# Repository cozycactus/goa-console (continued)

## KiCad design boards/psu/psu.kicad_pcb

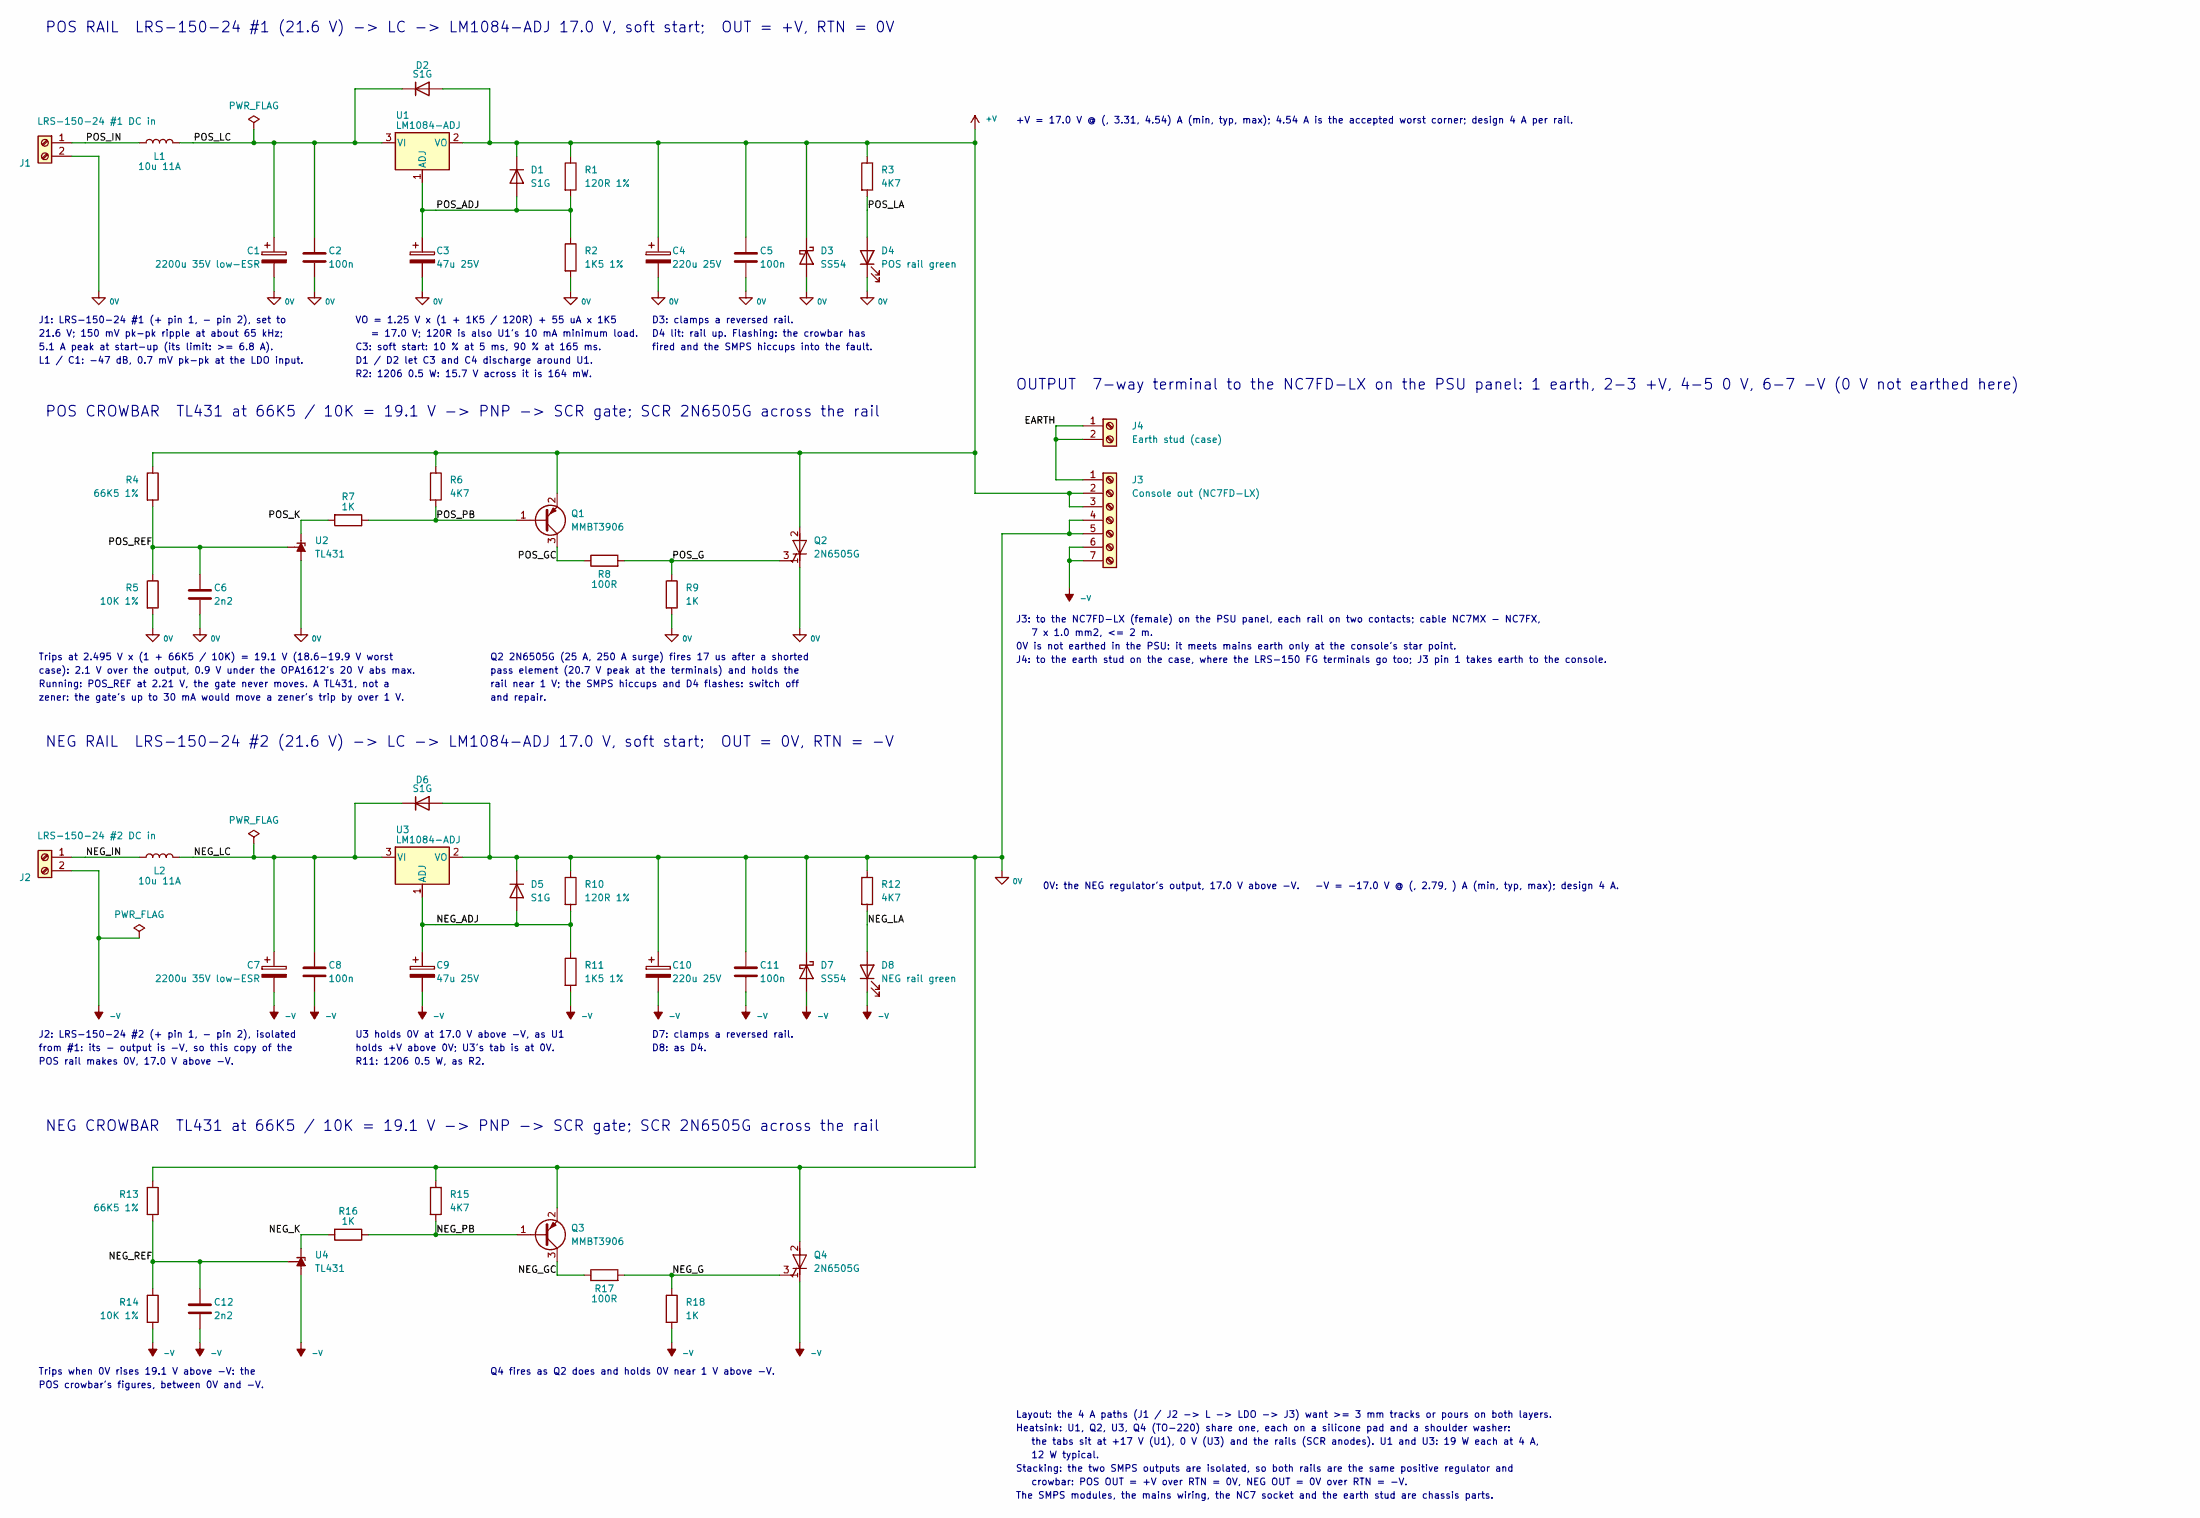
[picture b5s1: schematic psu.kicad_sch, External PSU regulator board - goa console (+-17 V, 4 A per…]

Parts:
C1, C7: 2200u 35V low-ESR; CP_Radial_D16.0mm_P7.50mm; MPN Rubycon 35ZLH2200MEFC16X25
C2, C5, C8, C11: 100n; C_0805_2012Metric; MPN Samsung CL21B104KBCNNNC (X7R 50V)
C3, C9: 47u 25V; CP_Radial_D6.3mm_P2.50mm; MPN Rubycon 63ZLH47MEFC6.3X11 (63V)
C4, C10: 220u 25V; CP_Radial_D8.0mm_P3.50mm; MPN Panasonic EEU-FR1E221
C6, C12: 2n2; C_0805_2012Metric; MPN KEMET C0805C222J5GACTU (C0G)
D1, D2, D5, D6: S1G; D_SMA; MPN Diodes S1G-13-F
D3, D7: SS54; D_SMC; MPN Diodes B540C-13-F (SS54 class, SMC 40 V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
D4: POS rail green; LED_D3.0mm; MPN Kingbright WP710A10GD
D8: NEG rail green; LED_D3.0mm; MPN Kingbright WP710A10GD
J1: LRS-150-24 #1 DC in; TerminalBlock_Phoenix_MKDS-1,5-2-5.08_1x02_P5.08mm_Horizont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; MPN Phoenix 1715721 MKDS 1,5/2-5,08
J2: LRS-150-24 #2 DC in; TerminalBlock_Phoenix_MKDS-1,5-2-5.08_1x02_P5.08mm_Horizont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; MPN Phoenix 1715721 MKDS 1,5/2-5,08
J3: Console out (NC7FD-LX); TerminalBlock_Phoenix_MKDS-1,5-7-5.08_1x07_P5.08mm_Horizont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; MPN Phoenix 1755897 MKDS 1,5/7-5,08 (to a N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
J4: Earth stud (case); TerminalBlock_Phoenix_MKDS-1,5-2-5.08_1x02_P5.08mm_Horizont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; MPN Phoenix 1715721 MKDS 1,5/2-5,08
L1, L2: 10u 11A; L_Toroid_Horizontal_D21.8mm_P19.10mm_Bourns_2100; MPN Bourns 2100LL-100-H-RC
Q1, Q3: MMBT3906; SOT-23; MPN onsemi MMBT3906LT1G
Q2, Q4: 2N6505G; TO-220-3_Vertical; MPN onsemi 2N6505G
R1, R10: 120R 1%; R_0805_2012Metric
R2, R11: 1K5 1%; R_1206_3216Metric; MPN Panasonic ERJ-P06F1501V
R3, R6, R12, R15: 4K7; R_0805_2012Metric
R4, R13: 66K5 1%; R_0805_2012Metric
R5, R14: 10K 1%; R_0805_2012Metric
R7, R9, R16, R18: 1K; R_0805_2012Metric
R8, R17: 100R; R_0805_2012Metric
U1, U3: LM1084-ADJ; TO-220-3_Vertical; MPN TI LM1084IT-ADJ/NOPB
U2, U4: TL431; SOT-23; MPN TI TL431AIDBZR

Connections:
/0V: C1.2, C2.2, C3.2, C4.2, C5.2, C6.2, C10.1, C11.1, D3.2 (A), D4.1 (K), D5.1 (K), D6.2 (A), D7.1 (K), J1.2, J3.4, J3.5, Q2.1 (K), Q3.2 (E), Q4.2 (A), R2.2, R5.2, R9.2, R10.1, R12.1, R13.1, R15.1, U2.3 (A), U3.2 (VO)
/+V: C4.1, C5.1, D1.1 (K), D2.2 (A), D3.1 (K), J3.2, J3.3, Q1.2 (E), Q2.2 (A), R1.1, R3.1, R4.1, R6.1, U1.2 (VO)
/-V: C7.2, C8.2, C9.2, C10.2, C11.2, C12.2, D7.2 (A), D8.1 (K), J2.2, J3.6, J3.7, Q4.1 (K), R11.2, R14.2, R18.2, U4.3 (A)
/EARTH: J3.1, J4.1, J4.2
/NEG_ADJ: C9.1, D5.2 (A), R10.2, R11.1, U3.1 (ADJ)
/NEG_G: Q4.3 (G), R17.2, R18.1
/NEG_GC: Q3.3 (C), R17.1
/NEG_IN: J2.1, L2.1
/NEG_K: R16.2, U4.1 (K)
/NEG_LA: D8.2 (A), R12.2
/NEG_LC: C7.1, C8.1, D6.1 (K), L2.2, U3.3 (VI)
/NEG_PB: Q3.1 (B), R15.2, R16.1
/NEG_REF: C12.1, R13.2, R14.1, U4.2 (REF)
/POS_ADJ: C3.1, D1.2 (A), R1.2, R2.1, U1.1 (ADJ)
/POS_G: Q2.3 (G), R8.2, R9.1
/POS_GC: Q1.3 (C), R8.1
/POS_IN: J1.1, L1.1
/POS_K: R7.2, U2.1 (K)
/POS_LA: D4.2 (A), R3.2
/POS_LC: C1.1, C2.1, D2.1 (K), L1.2, U1.3 (VI)
/POS_PB: Q1.1 (B), R6.2, R7.1
/POS_REF: C6.1, R4.2, R5.1, U2.2 (REF)

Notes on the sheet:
POS RAIL LRS-150-24 #1 (21.6 V) -> LC -> LM1084-ADJ 17.0 V, soft start; OUT = +V, RTN = 0V
POS CROWBAR TL431 at 66K5 / 10K = 19.1 V -> PNP -> SCR gate; SCR 2N6505G across the rail
J1: LRS-150-24 #1 (+ pin 1, - pin 2), set to
21.6 V; 150 mV pk-pk ripple at about 65 kHz;
5.1 A peak at start-up (its limit: >= 6.8 A).
L1 / C1: -47 dB, 0.7 mV pk-pk at the LDO input.
VO = 1.25 V x (1 + 1K5 / 120R) + 55 uA x 1K5
= 17.0 V; 120R is also U1's 10 mA minimum load.
C3: soft start: 10 % at 5 ms, 90 % at 165 ms.
D1 / D2 let C3 and C4 discharge around U1.
R2: 1206 0.5 W: 15.7 V across it is 164 mW.
D3: clamps a reversed rail.
D4 lit: rail up. Flashing: the crowbar has
fired and the SMPS hiccups into the fault.
Trips at 2.495 V x (1 + 66K5 / 10K) = 19.1 V (18.6-19.9 V worst
case): 2.1 V over the output, 0.9 V under the OPA1612's 20 V abs max.
Running: POS_REF at 2.21 V, the gate never moves. A TL431, not a
zener: the gate's up to 30 mA would move a zener's trip by over 1 V.
Q2 2N6505G (25 A, 250 A surge) fires 17 us after a shorted
pass element (20.7 V peak at the terminals) and holds the
rail near 1 V; the SMPS hiccups and D4 flashes: switch off
and repair.
OUTPUT 7-way terminal to the NC7FD-LX on the PSU panel: 1 earth, 2-3 +V, 4-5 0 V, 6-7 -V (0 V not earthed here)
+V = 17.0 V @ (, 3.31, 4.54) A (min, typ, max); 4.54 A is the accepted worst corner; design 4 A per rail.
0V: the NEG regulator's output, 17.0 V above -V. -V = -17.0 V @ (, 2.79, ) A (min, typ, max); design 4 A.
J3: to the NC7FD-LX (female) on the PSU panel, each rail on two contacts; cable NC7MX - NC7FX,
7 x 1.0 mm2, <= 2 m.
0V is not earthed in the PSU: it meets mains earth only at the console's star point.
J4: to the earth stud on the case, where the LRS-150 FG terminals go too; J3 pin 1 takes earth to the console.
Layout: the 4 A paths (J1 / J2 -> L -> LDO -> J3) want >= 3 mm tracks or pours on both layers.
Heatsink: U1, Q2, U3, Q4 (TO-220) share one, each on a silicone pad and a shoulder washer:
the tabs sit at +17 V (U1), 0 V (U3) and the rails (SCR anodes). U1 and U3: 19 W each at 4 A,
12 W typical.
Stacking: the two SMPS outputs are isolated, so both rails are the same positive regulator and
crowbar: POS OUT = +V over RTN = 0V, NEG OUT = 0V over RTN = -V.
The SMPS modules, the mains wiring, the NC7 socket and the earth stud are chassis parts.
NEG CROWBAR TL431 at 66K5 / 10K = 19.1 V -> PNP -> SCR gate; SCR 2N6505G across the rail
NEG RAIL LRS-150-24 #2 (21.6 V) -> LC -> LM1084-ADJ 17.0 V, soft start; OUT = 0V, RTN = -V
J2: LRS-150-24 #2 (+ pin 1, - pin 2), isolated
from #1: its - output is -V, so this copy of the

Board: 2 copper layers, 56 parts (0 on the bottom side), 22 nets, no tracks yet.

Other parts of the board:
H1, H2, H3, H4: M3 standoff; MountingHole_3.2mm_M3

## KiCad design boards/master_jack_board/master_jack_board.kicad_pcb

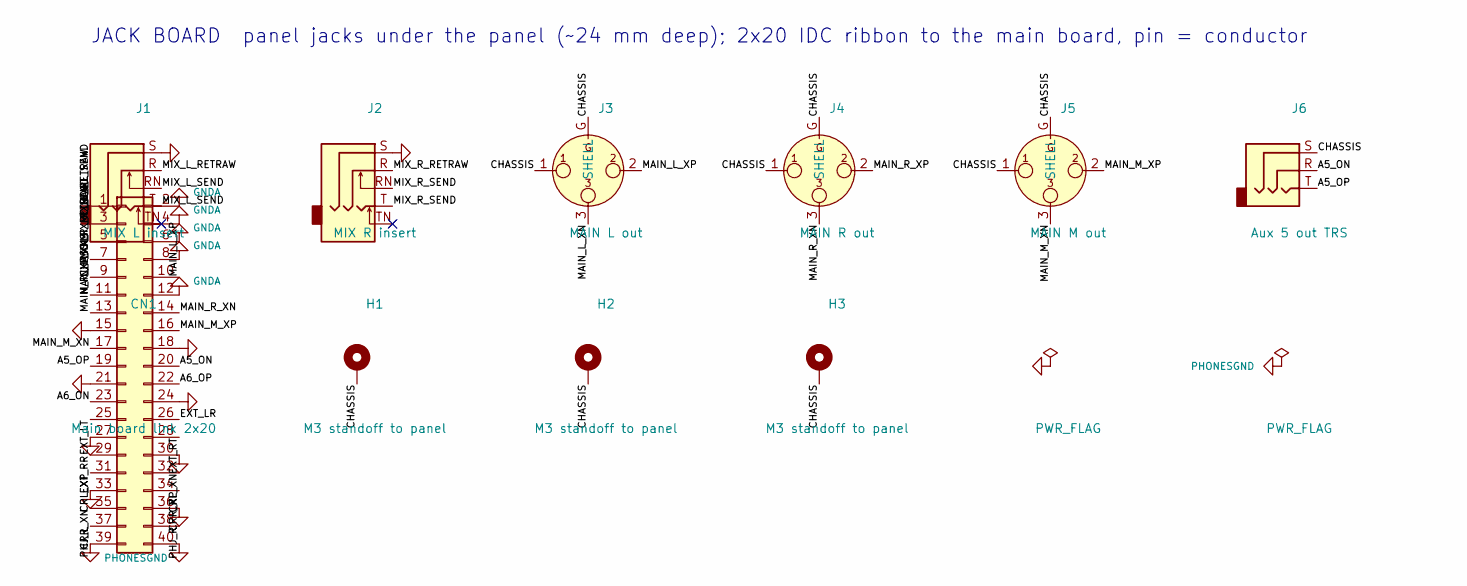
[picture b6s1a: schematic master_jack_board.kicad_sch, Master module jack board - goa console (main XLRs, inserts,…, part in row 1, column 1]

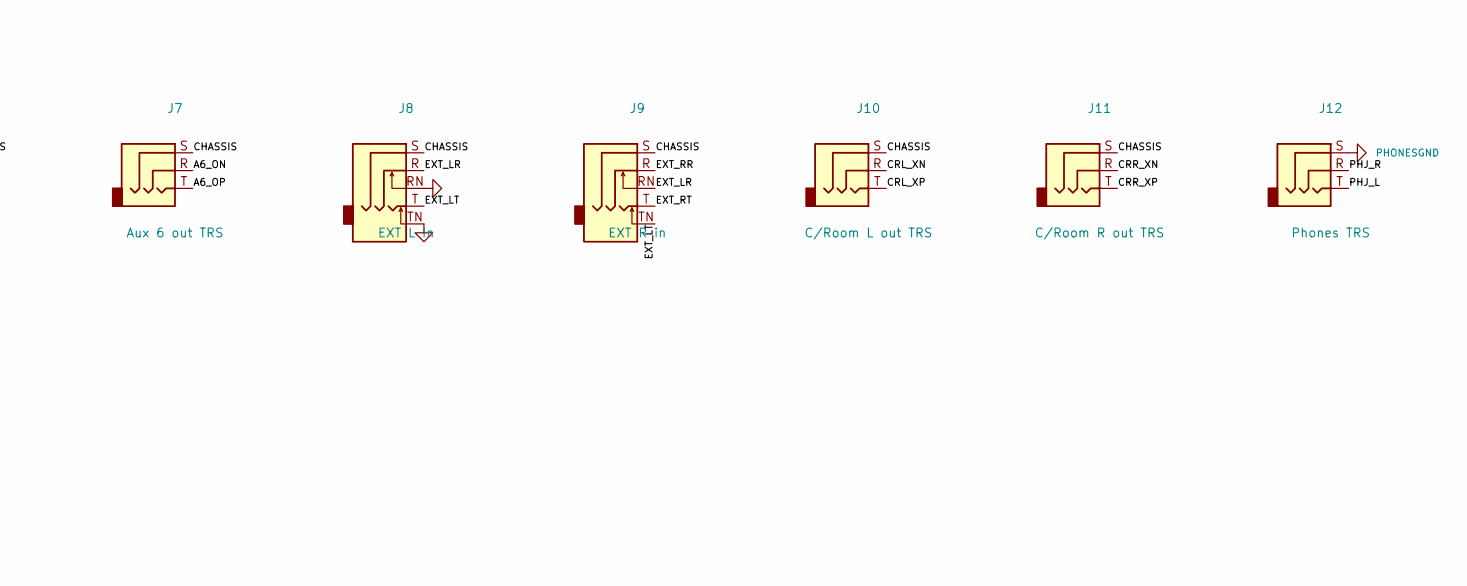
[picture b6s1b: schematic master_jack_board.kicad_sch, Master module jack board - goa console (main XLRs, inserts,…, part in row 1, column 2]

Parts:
CN1: Main board link 2x20; IDC-Header_2x20_P2.54mm_Vertical; MPN Wurth 61204021621 (2x20 box header)
H1, H2, H3: M3 standoff to panel; MountingHole_3.2mm_M3_Pad
J1: MIX L insert; Jack_6.35mm_Neutrik_NJ6FD-V_Vertical; MPN Neutrik NJ6FD-V
J2: MIX R insert; Jack_6.35mm_Neutrik_NJ6FD-V_Vertical; MPN Neutrik NJ6FD-V
J3: MAIN L out; Jack_XLR_Neutrik_NC3MAV_Vertical; MPN Neutrik NC3MAV
J4: MAIN R out; Jack_XLR_Neutrik_NC3MAV_Vertical; MPN Neutrik NC3MAV
J5: MAIN M out; Jack_XLR_Neutrik_NC3MAV_Vertical; MPN Neutrik NC3MAV
J6: Aux 5 out TRS; Jack_6.35mm_Neutrik_NJ6FD-V_Vertical; MPN Neutrik NJ6FD-V
J7: Aux 6 out TRS; Jack_6.35mm_Neutrik_NJ6FD-V_Vertical; MPN Neutrik NJ6FD-V
J8: EXT L in; Jack_6.35mm_Neutrik_NJ6FD-V_Vertical; MPN Neutrik NJ6FD-V
J9: EXT R in; Jack_6.35mm_Neutrik_NJ6FD-V_Vertical; MPN Neutrik NJ6FD-V
J10: C/Room L out TRS; Jack_6.35mm_Neutrik_NJ6FD-V_Vertical; MPN Neutrik NJ6FD-V
J11: C/Room R out TRS; Jack_6.35mm_Neutrik_NJ6FD-V_Vertical; MPN Neutrik NJ6FD-V
J12: Phones TRS; Jack_6.35mm_Neutrik_NJ6FD-V_Vertical; MPN Neutrik NJ6FD-V

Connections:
/A5_ON: CN1.20, J6.R
/A5_OP: CN1.19, J6.T
/A6_ON: CN1.23, J7.R
/A6_OP: CN1.22, J7.T
/CHASSIS: CN1.9, H1.1, H2.1, H3.1, J3.1, J3.G (SHELL), J4.1, J4.G (SHELL), J5.1, J5.G (SHELL), J6.S, J7.S, J8.S, J9.S, J10.S, J11.S
/CRL_XN: CN1.32, J10.R
/CRL_XP: CN1.31, J10.T
/CRR_XN: CN1.35, J11.R
/CRR_XP: CN1.34, J11.T
/EXT_LR: CN1.26, J8.R, J9.RN
/EXT_LT: CN1.25, J8.T, J9.TN
/EXT_RR: CN1.29, J9.R
/EXT_RT: CN1.28, J9.T
/MAIN_L_XN: CN1.11, J3.3
/MAIN_L_XP: CN1.10, J3.2
/MAIN_M_XN: CN1.17, J5.3
/MAIN_M_XP: CN1.16, J5.2
/MAIN_R_XN: CN1.14, J4.3
/MAIN_R_XP: CN1.13, J4.2
/MIX_L_RETRAW: CN1.3, J1.R
/MIX_L_SEND: CN1.1, J1.RN, J1.T
/MIX_R_RETRAW: CN1.7, J2.R
/MIX_R_SEND: CN1.5, J2.RN, J2.T
/PHJ_L: CN1.37, J12.T
/PHJ_R: CN1.38, J12.R
GNDA: CN1.2, CN1.4, CN1.6, CN1.8, CN1.12, CN1.15, CN1.18, CN1.21, CN1.24, CN1.27, CN1.30, CN1.33, CN1.36, CN1.40, J1.S, J2.S, J8.RN, J8.TN
PHONESGND: CN1.39, J12.S

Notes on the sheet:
JACK BOARD panel jacks under the panel (~24 mm deep); 2x20 IDC ribbon to the main board, pin = conductor

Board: 2 copper layers, 16 parts (1 on the bottom side), 27 nets, no tracks yet.

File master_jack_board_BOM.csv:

"Qty","Value","Footprint","MPN","DNP","References"
"1","Main board link 2x20","Connector_IDC:IDC-Header_2x20_P2.54mm_Vertical","Wurth 61204021621 (2x20 box header)","","CN1"
"1","MIX L insert","Connector_Audio:Jack_6.35mm_Neutrik_NJ6FD-V_Vertical","Neutrik NJ6FD-V","","J1"
"1","MIX R insert","Connector_Audio:Jack_6.35mm_Neutrik_NJ6FD-V_Vertical","Neutrik NJ6FD-V","","J2"
"1","MAIN L out","Connector_Audio:Jack_XLR_Neutrik_NC3MAV_Vertical","Neutrik NC3MAV","","J3"
"1","MAIN R out","Connector_Audio:Jack_XLR_Neutrik_NC3MAV_Vertical","Neutrik NC3MAV","","J4"
"1","MAIN M out","Connector_Audio:Jack_XLR_Neutrik_NC3MAV_Vertical","Neutrik NC3MAV","","J5"
"1","Aux 5 out TRS","Connector_Audio:Jack_6.35mm_Neutrik_NJ6FD-V_Vertical","Neutrik NJ6FD-V","","J6"
"1","Aux 6 out TRS","Connector_Audio:Jack_6.35mm_Neutrik_NJ6FD-V_Vertical","Neutrik NJ6FD-V","","J7"
"1","EXT L in","Connector_Audio:Jack_6.35mm_Neutrik_NJ6FD-V_Vertical","Neutrik NJ6FD-V","","J8"
"1","EXT R in","Connector_Audio:Jack_6.35mm_Neutrik_NJ6FD-V_Vertical","Neutrik NJ6FD-V","","J9"
"1","C/Room L out TRS","Connector_Audio:Jack_6.35mm_Neutrik_NJ6FD-V_Vertical","Neutrik NJ6FD-V","","J10"
"1","C/Room R out TRS","Connector_Audio:Jack_6.35mm_Neutrik_NJ6FD-V_Vertical","Neutrik NJ6FD-V","","J11"
"1","Phones TRS","Connector_Audio:Jack_6.35mm_Neutrik_NJ6FD-V_Vertical","Neutrik NJ6FD-V","","J12"

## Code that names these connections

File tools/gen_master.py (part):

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
# ================================================================ PART 5: power entry, grounding  [24-26]
b = block('POWER ENTRY  (7-pin XLR NC7MD-LX on the rear panel, two 5 A contacts per rail, 18 AWG to this terminal; +-17 V PSU)')
# terminal = XLR pin: 1 earth (pin 1 mates first), 2-3 +V, 4-5 0 V, 6-7 -V; up to ~3.8 A per rail (spec 27)
P(b, ref('J'), 'PWRIN', 'PSU in (NC7MD-LX)', {1: 'CHASSIS', 2: '+VBUS', 3: '+VBUS', 4: 'GNDA', 5: 'GNDA',
                                              6: '-VBUS', 7: '-VBUS'})
P(b, ref('D'), 'DS', 'SS54', {1: '+VBUS', 2: 'GNDA'}); P(b, ref('D'), 'DS', 'SS54', {1: 'GNDA', 2: '-VBUS'})
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b = block('GROUND CANCEL BUFFER  (feeds every re-inverter; summing amps use the raw GCANCEL line; 100K keeper)')
amp(b, 'GCANCEL', 'GCANCEL_BUF', 'GCANCEL_BUF')     # output straight to the net: no series R outside the loop, <= 50 pF
gcu = LAST[0]; frag(b, 16, 9, lambda d: frags.follower(d, 'GCANCEL', 'GCANCEL_BUF', gcu))
rk = R(b, '100K', 'GCANCEL', 'GNDA')     # keeper: defines the line with no strip or group on a wing; leaks -79 dB at N = 32
chain(b, 'GCANCEL', [('g', rk)])

# ================================================================ PART 1: stereo mix  [1-8]
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    summer(b, bus, f'SUM_{side}', '4K7', '100p')
    reinv(b, f'SUM_{side}', f'MIX_{side}')
    insert(b, f'MIX_{side}', f'PRE_{side}', f'MIX_{side}')
b = block('MASTER FADER (dual 100 mm A10K, pin 1 = GNDA) + post-amps +10 dB')
rvf = ref('RV'); P(b, rvf, 'POT2', 'Master fader 10K log 100mm dual', {1: 'GNDA', 3: 'PRE_L', 2: 'MW_L', 4: 'GNDA', 6: 'PRE_R', 5: 'MW_R'},
  fp=FADER2_FP, mpn='Bourns PTB0144-2010BPA103')
frag(b, 14, 8, lambda d: frags.pot2(d, rvf))
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amp(b, 'GNDA', 'MONO_N', 'MONO_INV'); mu1 = LAST[0]; mf, mc = R(b, '10K', 'MONO_INV', 'MONO_N'), C(b, '100p C0G', 'MONO_INV', 'MONO_N')
frag(b, 24, 15, lambda d: frags.inv(d, 'POST_L', 'MONO_INV', mu1, m1, mf, mc, 'GNDA', 'POST_R', m2))
m3, m4 = R(b, '10K', 'MONO_INV', 'MONO_N2'), R(b, '10K', 'MONO_N2', 'MONO'); c = C(b, '22p C0G', 'MONO', 'MONO_N2')
near(c, amp(b, 'GNDA', 'MONO_N2', 'MONO'))              # 22p: stability against the input capacitance, at the pins
mu2 = LAST[0]; frag(b, 24, 15, lambda d: frags.inv(d, 'MONO_INV', 'MONO', mu2, m3, m4, c, 'GNDA'))
spares(b)       # the summer area's odd op-amp half stays a spare: a later block would pull its package to another zone
b = block('MAIN OUTPUTS: DRV134 -> 10u NP in the Sense loop -> mute relay (NO; NC grounds the line) -> XLR male, pin 2 hot')
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
# ================================================================ PART 4: monitoring  [17-22]
b = block('EXT INPUT (2-track / DAW) and MIX / EXT monitor select  (SW latched = EXT)')
# outputs EXT_BL/BR (EXT_RR was the R jack's ring: docs/reviews/master_group_review.md MG1); 100R build-out at the pin, because
# with EXT selected the receivers drive the EXT -> SW -> MON -> DG413 run
for sd, u in zip('LR', stereo_in(b, 'EXT', 'EXT_BL', 'EXT_BR')):
    rb = R(b, '100R', f'EXT_B{sd}', f'EXT_B{sd}O'); near(rb, u)
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# The clamp keeps PFLDET from back-feeding the released keys' 100K + 4K7 + LED paths (24 presses read 1.29 V, released
# LEDs <= 20 nA); the 1u filters the PVA2's <= 3 ms bounce (one threshold crossing per press); 10M adds ~20 mV
# hysteresis. Both comparators sink while no key is pressed: A is the DG413 logic (MON), B holds the flasher off
pd1, pr1, pr2 = R(b, '10K', 'PFLDET', 'GNDD'), R(b, '330K', '+VL', 'PFL_REF'), R(b, '10K', 'PFL_REF', 'GNDD')
pdd1, pdd2, pdc = D(b, 'PFLDET', 'PFL_CL'), D(b, 'PFL_CL', 'GNDD'), C(b, '1u', 'PFLDET', 'GNDD')
chain(b, '+VL', [('s', pr1), ('g', pr2)], 'PFL_REF'); chain(b, 'PFLDET', [('g', pd1), ('g', pdc), ('s', pdd1), ('g', pdd2)])
with new_package('LM393', 'VL'):        # one package for both, beside the DG413 so PFL_ON_RAW stays short
    pc = cmp(b, 'PFLDET', 'PFL_REF', 'PFL_ON_RAW'); pa = LAST[0]; cmp(b, 'PFLDET', 'PFL_REF', 'FL_HOLD'); pb = LAST[0]
frag(b, 20, 18, lambda d: frags.comparators(d, [(pa, False), (pb, False)]))
pu1, ph1 = R(b, '100K', '+5VL', 'PFL_ON_RAW'), R(b, '10M', 'PFL_ON_RAW', 'PFLDET'); near(pu1, pc); near(ph1, pc)   # logic level, hysteresis
r = R(b, '10K', 'PFL_ON_RAW', 'PFL_ON'); near(r, dg); near(pc, r)    # bounds IN clamp current while rails settle
chain(b, '+5VL', [('s', pu1)], 'PFL_ON_RAW'); chain(b, 'PFL_ON_RAW', [('s', ph1)], 'PFLDET'); chain(b, 'PFL_ON_RAW', [('s', r)], 'PFL_ON')

b = block('RUDE SOLO: ~2 Hz flasher, PFL ACTIVE LED; held off through FL_N while no key is pressed')
# while released, the hold comparator pulls FL_N to about -VL through the 1N4148, so FL_OUT stays high (LED off); on a
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
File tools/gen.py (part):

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# A 1/4" plug goes ~30 mm deep, so the jacks sit on their own board ~24 mm under the panel (the main board is at
# 11.5 mm), joined to the main board by a 10-way IDC ribbon: CN3 (main board, bottom side) <-> CN5 (jack board).
JACK_V = 'Connector_Audio:Jack_6.35mm_Neutrik_NJ6FD-V_Vertical'; JACK_V_MPN = 'Neutrik NJ6FD-V'
# ribbon conductor = pin number: each pair adjacent, grounds between input, send, return and direct out
LINK = {1: 'IN_T', 2: 'IN_R', 3: 'GNDA', 4: 'SEND', 5: 'GNDA', 6: 'RET_RAW', 7: 'GNDA', 8: 'DO_T', 9: 'DO_R', 10: 'GNDA'}
POT2A = 'Alpha RD902F-40-15R1-A10K (dual, log)'

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b = block('FADER + POST-AMP (+10 dB; omit R38 for unity)  JP1 = VCA bypass')
P(b,'RV1','POT','Fader 10K log 100mm',{1:'GNDA',3:'MUTEOUT',2:'WIPER'},fp=FADER_FP,mpn='Bourns PTB0143-2010BPA103')
P(b,'C13','C','2.2u film',{1:'WIPER',2:'VCAIN'},fp=FILM_2U2)
P(b,'JP1','SJ2','VCA bypass',{1:'VCAIN',2:'FPIN'}); P(b,'R18','R','100K',{1:'FPIN',2:'GNDA'})
# VCA module option (spec 7.1): SSI2162 + I/V + inverter on a plug-in module; JP1 bridged when not fitted
P(b,'J3','CONN6','VCA module socket',{1:'VCAIN',2:'FPIN',3:'VCA_CTRL',4:'+VA',5:'GNDA',6:'-VA'},dnp=True)
P(b,'J4','CONN2','VCA control in',{1:'VCA_CTRL',2:'GNDA'},dnp=True); P(b,'R44','R','100K',{1:'VCA_CTRL',2:'GNDA'},dnp=True)
P(b,'U2','OPA','OPA1612',{3:'FPIN',2:'U2A_N',1:'FPOST'},unit=1)
P(b,'U2','OPA','OPA1612',{5:'GNDA',6:'U2B_O',7:'U2B_O'},unit=2)   # spare half, tied off (PAN1: pan L moved to U8B)
P(b,'C82','C','10p C0G',{1:'FPIN',2:'GNDA'},fp=C0G)   # not above 22p: it sits on U3B's output with the fader at top
P(b,'R19','R','4K7',{1:'FPOST',2:'U2A_N'}); P(b,'C14','C','100p C0G',{1:'FPOST',2:'U2A_N'})
P(b,'R38','R','2K2',{1:'U2A_N',2:'GNDA'})
P(b,'C15','C','100u NP 25V',{1:'FPOST',2:'POST'},fp=CAP_FP['220u']); P(b,'R35','R','47K',{1:'POST',2:'GNDA'})
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# ---------------------------------------------------------------- jack board (its own PCB; same net names)
def jack_board_draw(d):
    """The link at the left, the three jacks at the right facing it, every signal a wire: the link's right-hand pins
    straight from the jacks; IN_T goes over the link to pin 1 and DO_R under it to pin 9, the two that are on its
    left side."""
    XL, YL, XJ = 16, 15, 50                                    # the link (pin rows YL - 2 .. YL + 2), the jacks' column
    L, Rr = XL - 2, XL + 3                                     # its pin columns
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
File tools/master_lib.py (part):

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 'OPA1656': ('Amplifier_Operational', 'OPA1656ID'), 'TL072': ('Amplifier_Operational', 'TL072'),
 'LM2901': ('Comparator', 'LM2901'), 'LME49600': ('Amplifier_Audio', 'LME49600'),
 'DRV134': ('goa-console', 'DRV134'), 'RELAY': ('Relay', 'G6K-2'),
 'XLR3': ('goa-console', 'XLR3_Shell'),   # pin G = the NC3MAV / NC3MAH shell pad, on CHASSIS (2026-10-28)
 'PWRIN': ('Connector', 'Screw_Terminal_01x07'),
 'FB': ('Device', 'FerriteBead'), 'PTC': ('Device', 'Polyfuse'), 'DS': ('Device', 'D_Schottky'),
 'DZ': ('Device', 'D_Zener'), 'NPN': ('Transistor_BJT', 'MMBT3904'), 'PNP': ('Transistor_BJT', 'BCP53'),
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    fin, fn, fo = name + '_FIN', name + '_FN', name + '_FPOST'
    cin, rsh = C(b, '2.2u', wiper, fin), R(b, '100K', fin, 'GNDA')
    u = amp(b, fin, fn, fo); uu = LAST[0]
    # 10p: the wiper's 1-2.5 kohm against Cdiff; 47R build-out at the pin, outside the loop, so POST's run and the
    # DG413 on-capacitance (master) or the pan pot (group) don't load the follower (docs/reviews/master_group_review.md MG4)
    csh, rb = C(b, '10p C0G', fin, 'GNDA'), R(b, '47R', fo, fo + 'O'); near(csh, u); near(rb, u)
    rf, cf, rg = R(b, '4K7', fo, fn), C(b, '100p C0G', fo, fn), R(b, '2K2', fn, 'GNDA')
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    assert not {outl, outr} & {lt, lr, rt, rr}, 'receiver output named like a jack net'
    # sleeves on CHASSIS (docs/studies/ground_study.md G2): cable-shield currents go to the panel, not through GNDA
    # L's own normals short an empty L input (and, through R's normals, an empty R): the 1M bias would hiss (G3b)
    jack(b, 'JACKSW', (label or name) + ' L in', {'T': lt, 'R': lr, 'S': 'CHASSIS', 'TN': 'GNDA', 'RN': 'GNDA'})
    jack(b, 'JACKSW', (label or name) + ' R in', {'T': rt, 'R': rr, 'S': 'CHASSIS', 'TN': lt, 'RN': lr})
    return receiver(b, lt, lr, outl), receiver(b, rt, rr, outr)

# ---------------------------------------------------------------- jack boards
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    if jackboard is None: P(b, ref('J'), key, value, pins)
    else: jackboard.append(dict(key=key, value=value, pins=pins, split=split))

def link_pins(jacks, ground='GNDA', own_ground=('PHONESGND',), skip=()):
    """IDC pinout for the jack-board link: each jack's signals adjacent, then a ground; a group that carries its
    own signal return (phones) gets none. Ribbon conductor = pin number. skip: nets that stay on the jack board
    (CHASSIS where the standoffs bond it to the panel). Returns (n, {pin: net})."""
    pins, seen = [], set(skip)
    for j in jacks:
        nets = [n for n in j['pins'].values() if n not in ('NC', ground) and n not in seen and not seen.add(n)]
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    for n2, link2, value in more: link_header(b, n2, link2, value)
    for i in range(1, holes + 1): P(b, f'H{i}', 'MHPAD', 'M3 standoff to panel', {1: 'CHASSIS'})
    P(b, '#FLG01', 'FLAG', 'PWR_FLAG', {1: 'GNDA'})
    if any('PHONESGND' in j['pins'].values() for j in jacks):         # a power symbol too: driven here as well
        P(b, '#FLG02', 'FLAG', 'PWR_FLAG', {1: 'PHONESGND'})
    project_file(out)
    build(out, project, title, {1: 'Generated with its main board (master_lib.jack_board)', 2: 'Link pinout = main board CN'},
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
